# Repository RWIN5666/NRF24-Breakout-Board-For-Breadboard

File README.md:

# NRF24 Breakout Board For Breadboard

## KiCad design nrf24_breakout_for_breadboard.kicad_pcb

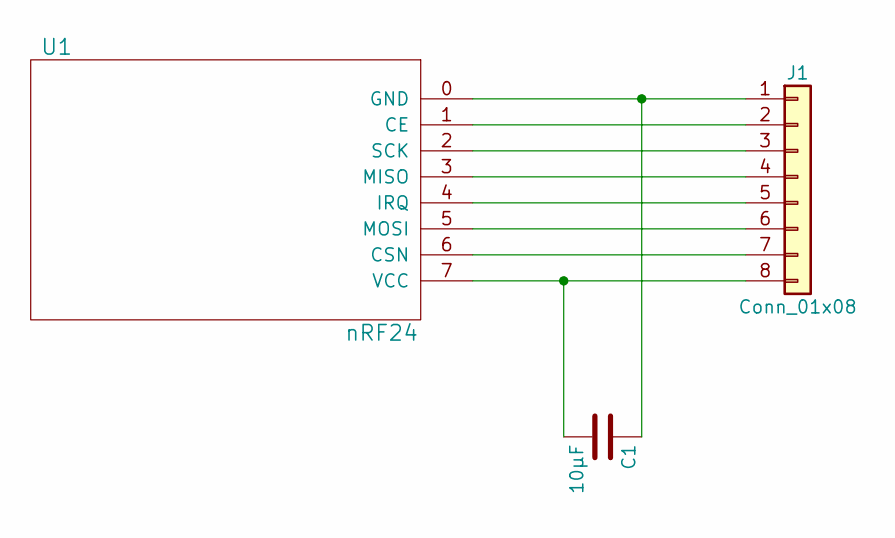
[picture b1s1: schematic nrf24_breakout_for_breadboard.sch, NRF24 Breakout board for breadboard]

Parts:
C1: 10µF; C_0805
J1: Conn_01x08; Pin_Header_Straight_1x08_Pitch2.54mm
U1: nRF24

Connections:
unnamed: C1.1, J1.1, U1.0 (GND)
unnamed: C1.2, J1.8, U1.7 (VCC)
unnamed: J1.2, U1.1 (CE)
unnamed: J1.3, U1.2 (SCK)
unnamed: J1.4, U1.3 (MISO)
unnamed: J1.5, U1.4 (IRQ)
unnamed: J1.6, U1.5 (MOSI)
unnamed: J1.7, U1.6 (CSN)

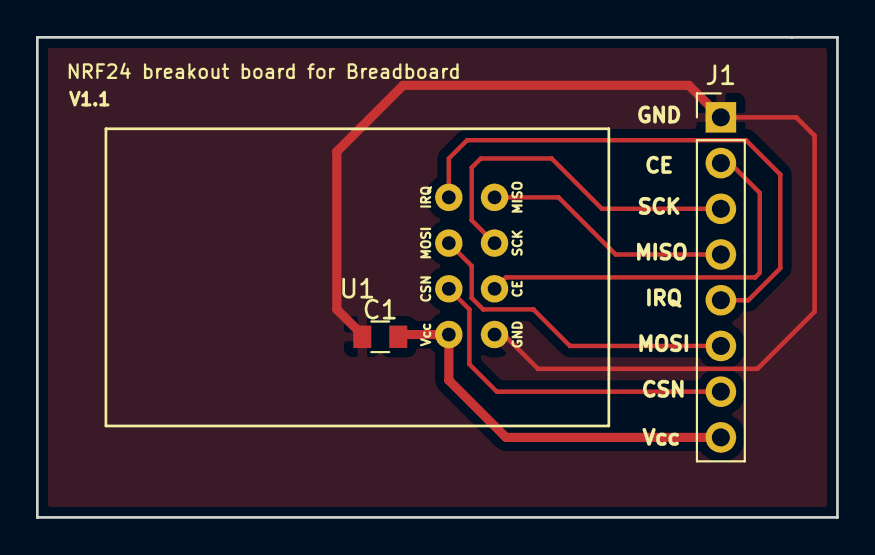
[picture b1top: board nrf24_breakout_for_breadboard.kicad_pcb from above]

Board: 2 copper layers, 44.5 x 26.7 mm, 3 parts (0 on the bottom side), 8 nets.

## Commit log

2018-03-19 Initial commit.
    Project contains GERBER outputs for manufacturing and design files.
